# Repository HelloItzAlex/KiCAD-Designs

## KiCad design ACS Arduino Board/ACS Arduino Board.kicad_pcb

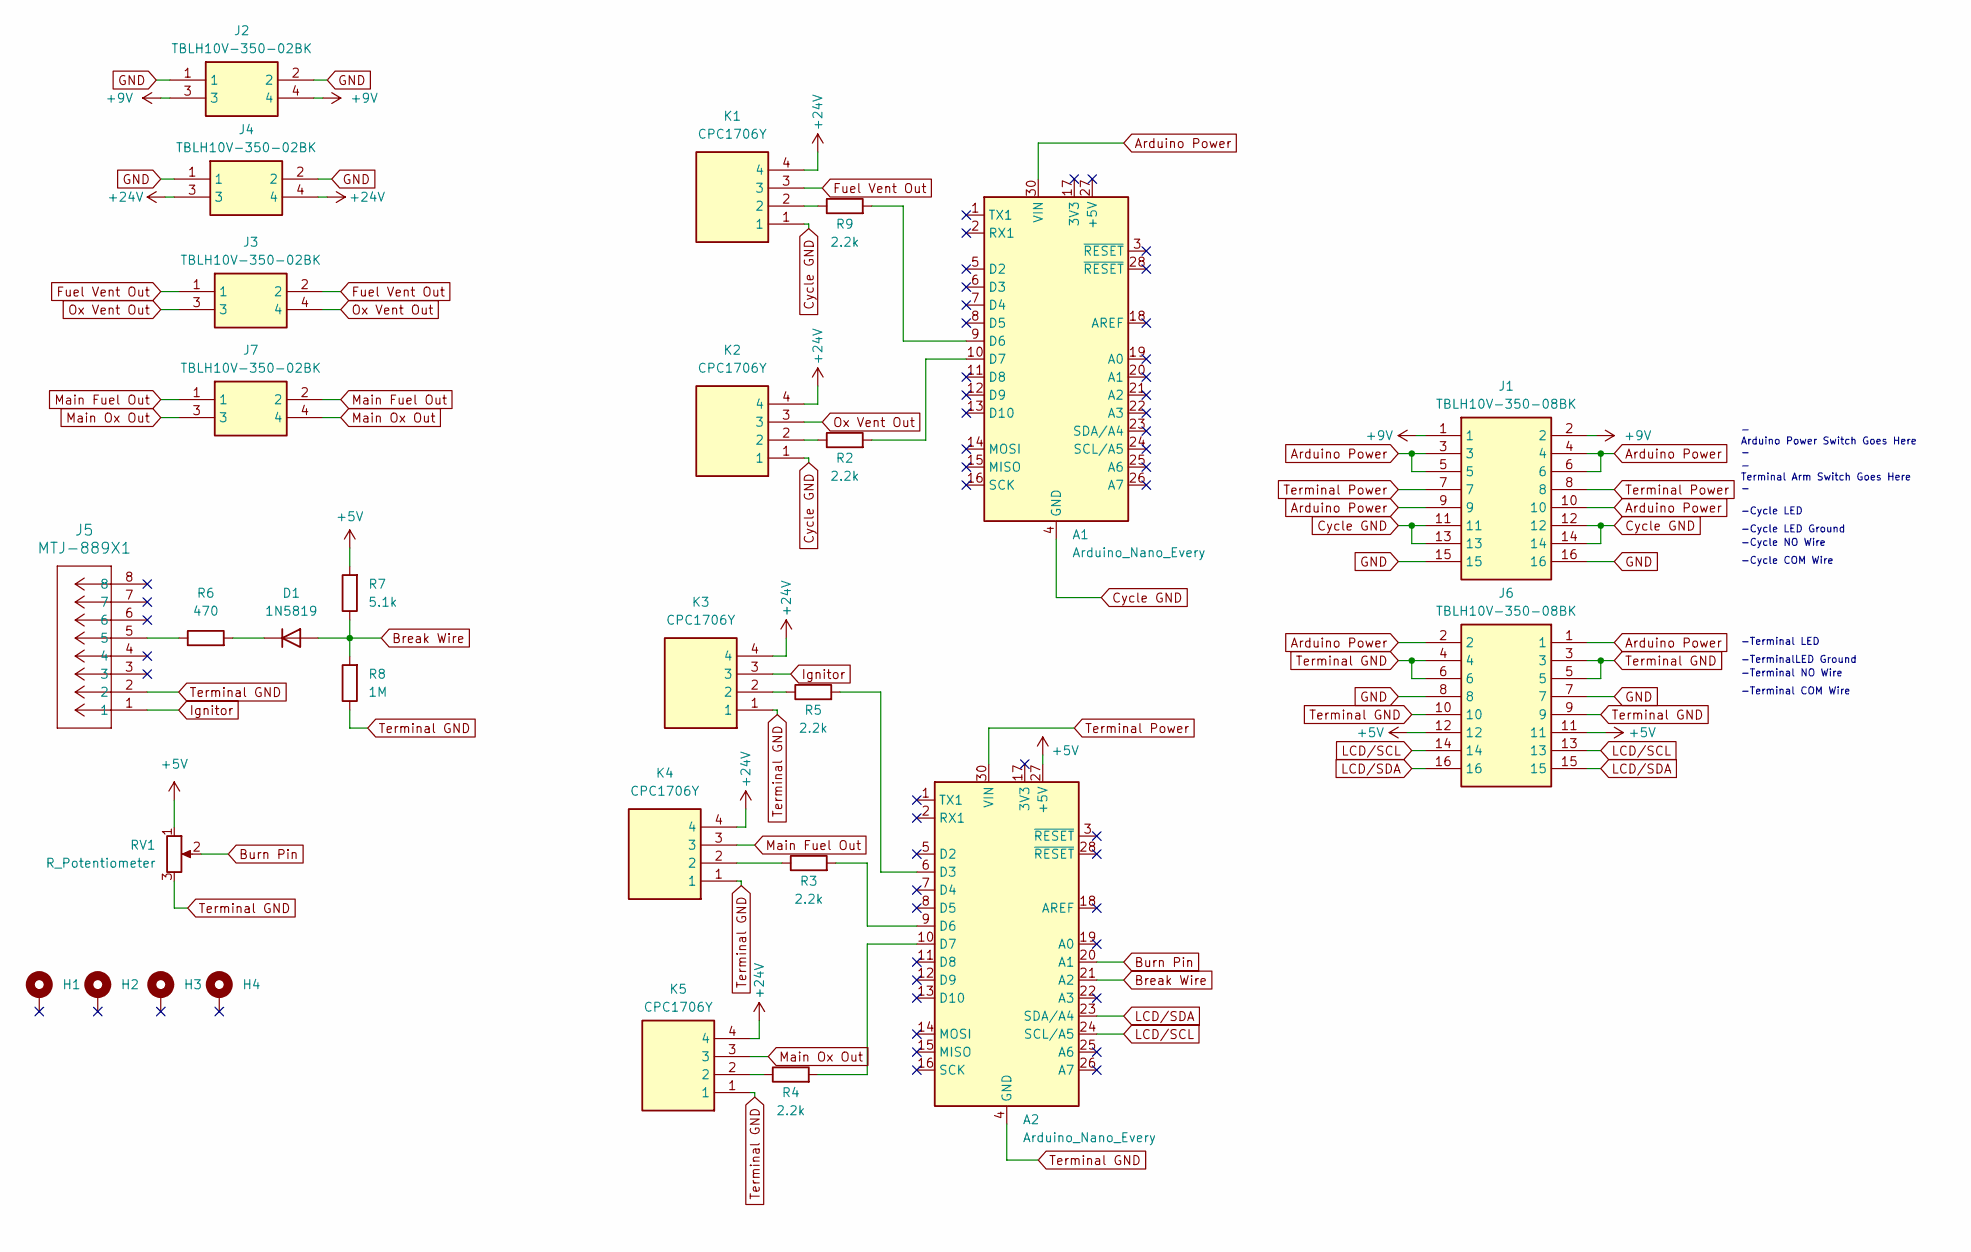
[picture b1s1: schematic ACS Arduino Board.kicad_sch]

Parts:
A1, A2: Arduino_Nano_Every; Arduino_Nano
D1: 1N5819; D_A-405_P7.62mm_Horizontal
H1, H2, H3, H4: MountingHole_Pad; MountingHole_3.2mm_M3_DIN965_Pad_TopBottom
J1, J6: TBLH10V-350-08BK; RHDR16W80P550X350_2X8_2870X850X1420P; Mouser Part Number 490-TBLH10V-350-08BK
J2, J3, J4, J7: TBLH10V-350-02BK; RHDR4W80P550X350_2X2_770X850X1420P; Mouser Part Number 490-TBLH10V-350-02BK
J5: MTJ-889X1; CONN_MTJ-889X1_ADM
K1, K2, K3, K4, K5: CPC1706Y; Mouser Part Number 849-CPC1706Y
R2, R3, R4, R5, R9: 2.2k; R_Axial_DIN0207_L6.3mm_D2.5mm_P7.62mm_Horizontal
R6: 470; R_Axial_DIN0207_L6.3mm_D2.5mm_P7.62mm_Horizontal
R7: 5.1k; R_Axial_DIN0207_L6.3mm_D2.5mm_P7.62mm_Horizontal
R8: 1M; R_Axial_DIN0207_L6.3mm_D2.5mm_P7.62mm_Horizontal
RV1: R_Potentiometer; PinSocket_1x03_P2.54mm_Vertical

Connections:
+5V: A2.27 (+5V), J6.11, J6.12, R7.2, RV1.1
+9V: J1.1, J1.2, J2.3, J2.4
+24V: J4.3, J4.4, K1.4, K2.4, K3.4, K4.4, K5.4
Arduino Power: A1.30 (VIN), J1.3, J1.4, J1.5, J1.6, J1.9, J1.10, J6.1, J6.2
Break Wire: A2.21 (A2), D1.2 (A), R7.1, R8.2
Burn Pin: A2.20 (A1), RV1.2
Cycle GND: A1.4 (GND), A1.29 (GND), J1.11, J1.12, J1.13, J1.14, K1.1, K2.1
Fuel Vent Out: J3.1, J3.2, K1.3
GND: J1.15, J1.16, J2.1, J2.2, J4.1, J4.2, J6.7, J6.8
Ignitor: J5.1, K3.3
LCD/SCL: A2.24 (SCL/A5), J6.13, J6.14
LCD/SDA: A2.23 (SDA/A4), J6.15, J6.16
Main Fuel Out: J7.1, J7.2, K4.3
Main Ox Out: J7.3, J7.4, K5.3
unnamed: A1.9 (D6), R9.2
unnamed: A1.10 (D7), R2.2
unnamed: A2.6 (D3), R5.2
unnamed: A2.9 (D6), R3.2
unnamed: A2.10 (D7), R4.2
unnamed: D1.1 (K), R6.2
unnamed: J5.5, R6.1
unnamed: K1.2, R9.1
unnamed: K2.2, R2.1
unnamed: K3.2, R5.1
unnamed: K4.2, R3.1
unnamed: K5.2, R4.1
Ox Vent Out: J3.3, J3.4, K2.3
Terminal GND: A2.4 (GND), A2.29 (GND), J5.2, J6.3, J6.4, J6.5, J6.6, J6.9, J6.10, K3.1, K4.1, K5.1, R8.1, RV1.3
Terminal Power: A2.30 (VIN), J1.7, J1.8

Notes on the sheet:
-Cycle LED Ground
-Cycle NO Wire
-Cycle LED
- Terminal Arm Switch Goes Here -
-Terminal LED
-TerminalLED Ground
-Terminal COM Wire
- Arduino Power Switch Goes Here -
-Cycle COM Wire
-Terminal NO Wire

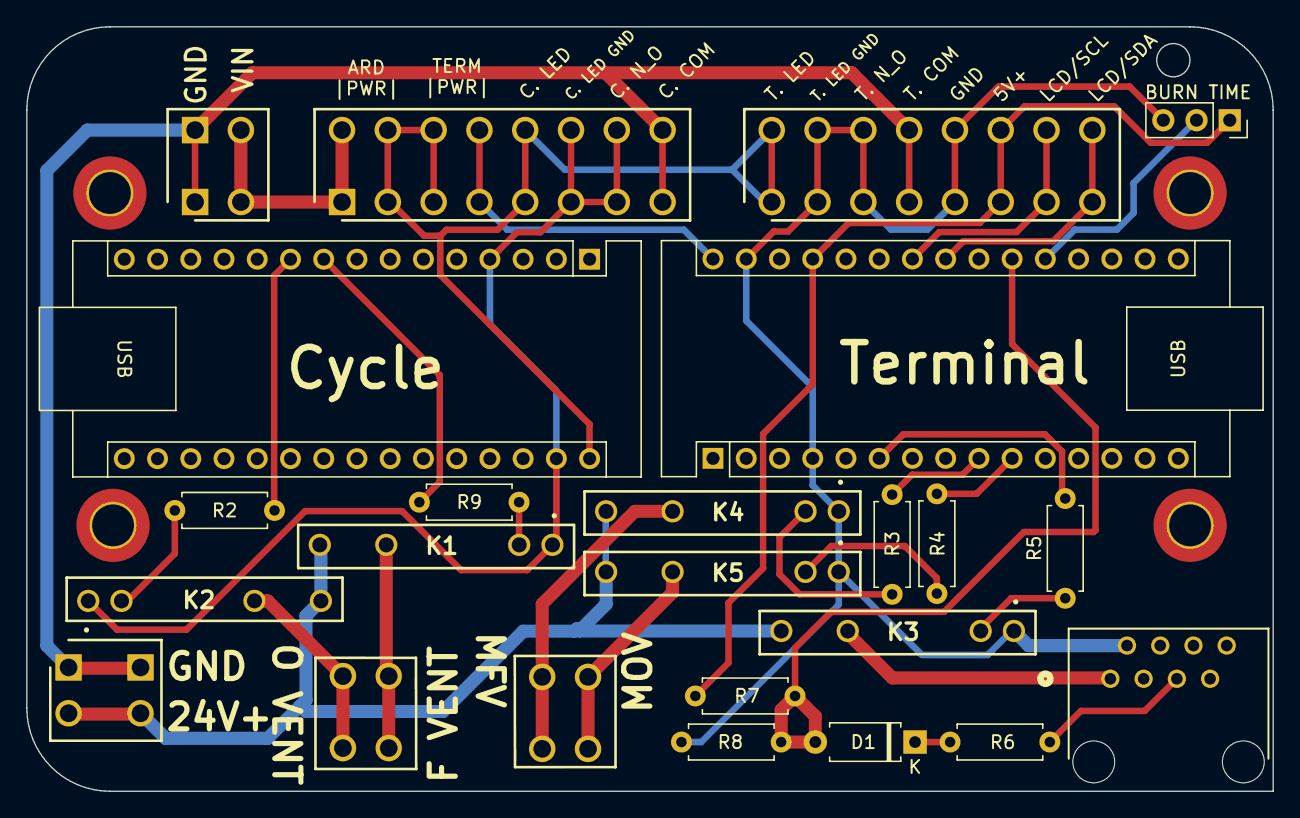
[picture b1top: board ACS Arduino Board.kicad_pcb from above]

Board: 2 copper layers, 95.2 x 58.4 mm, 28 parts (0 on the bottom side), 29 nets.

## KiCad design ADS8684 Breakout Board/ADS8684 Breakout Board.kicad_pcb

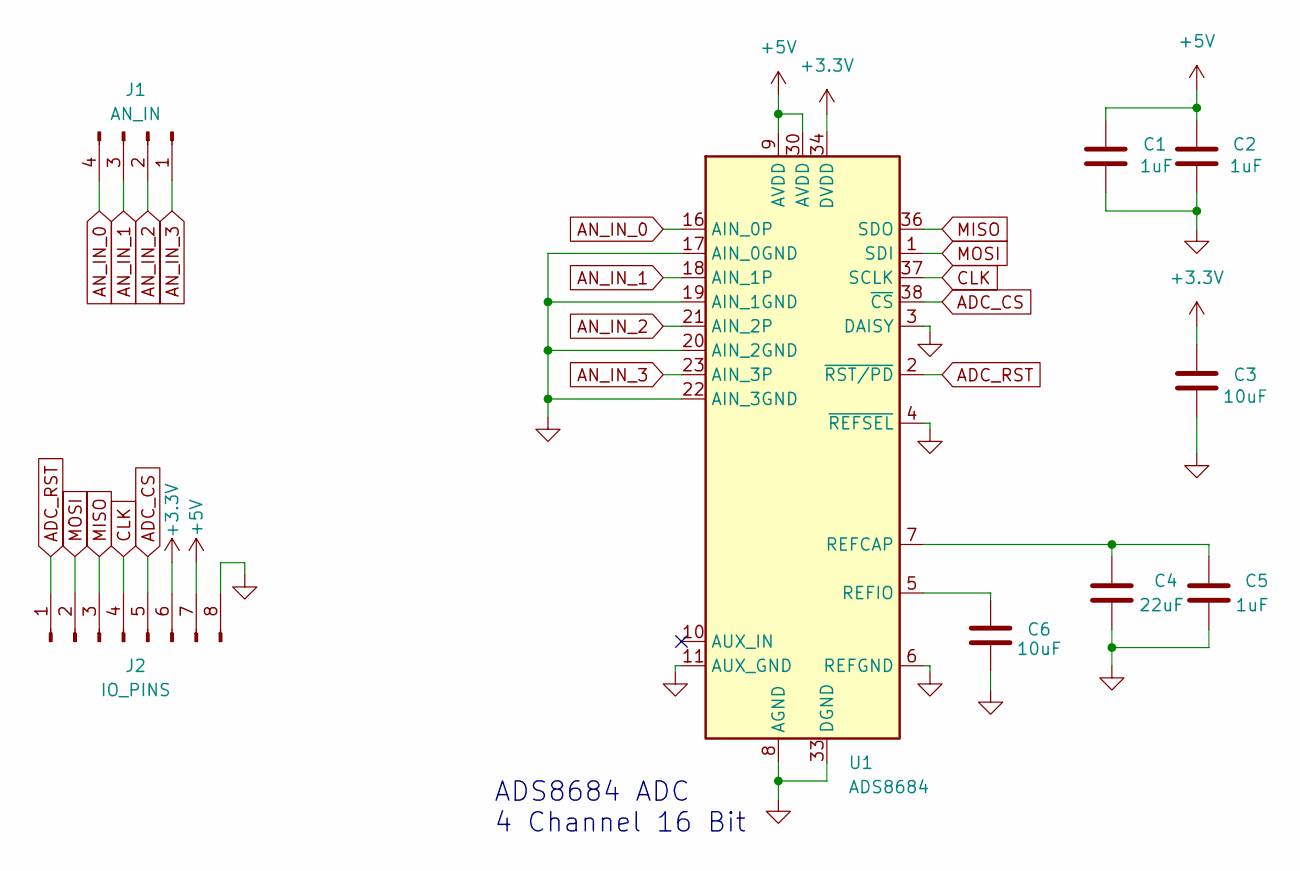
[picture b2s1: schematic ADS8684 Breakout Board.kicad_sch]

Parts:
C1, C2, C5: 1uF; C_0603_1608Metric
C3: 10uF; C_0805_2012Metric
C4: 22uF; C_1210_3225Metric
C6: 10uF; C_0603_1608Metric
J1: AN_IN; PinHeader_1x04_P2.54mm_Vertical
J2: IO_PINS; PinHeader_1x08_P2.54mm_Vertical
U1: ADS8684; TSSOP-38_4.4x9.7mm_P0.5mm

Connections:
+3.3V: C3.2, J2.6, U1.34 (DVDD)
+5V: C1.2, C2.2, J2.7, U1.9 (AVDD), U1.30 (AVDD)
ADC_CS: J2.5, U1.38 (~CS)
ADC_RST: J2.1, U1.2 (~RST/PD)
AN_IN_0: J1.4, U1.16 (AIN_0P)
AN_IN_1: J1.3, U1.18 (AIN_1P)
AN_IN_2: J1.2, U1.21 (AIN_2P)
AN_IN_3: J1.1, U1.23 (AIN_3P)
CLK: J2.4, U1.37 (SCLK)
GND: C1.1, C2.1, C3.1, C4.1, C5.1, C6.2, J2.8, U1.3 (DAISY), U1.4 (~REFSEL), U1.6 (REFGND), U1.8 (AGND), U1.11 (AUX_GND), U1.17 (AIN_0GND), U1.19 (AIN_1GND), U1.20 (AIN_2GND), U1.22 (AIN_3GND), U1.28 (AGND), U1.29 (AGND), U1.31 (AGND), U1.32 (AGND), U1.33 (DGND)
MISO: J2.3, U1.36 (SDO)
MOSI: J2.2, U1.1 (SDI)
unnamed: C4.2, C5.2, U1.7 (REFCAP)
unnamed: C6.1, U1.5 (REFIO)

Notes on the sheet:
ADS8684 ADC 4 Channel 16 Bit

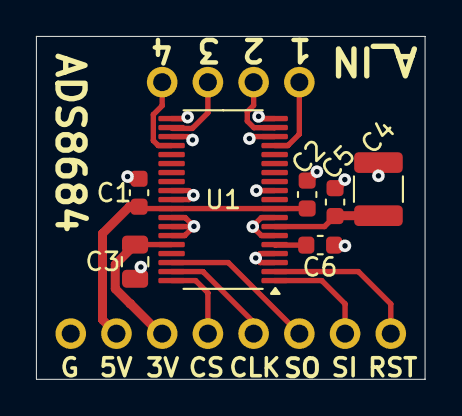
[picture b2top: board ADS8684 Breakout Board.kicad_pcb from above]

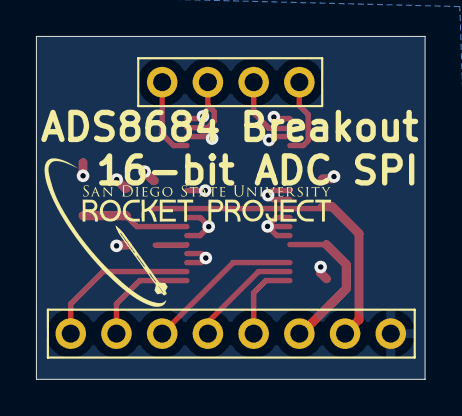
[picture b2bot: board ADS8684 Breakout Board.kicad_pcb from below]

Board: 2 copper layers, 21.6 x 19.1 mm, 9 parts (2 on the bottom side), 14 nets.

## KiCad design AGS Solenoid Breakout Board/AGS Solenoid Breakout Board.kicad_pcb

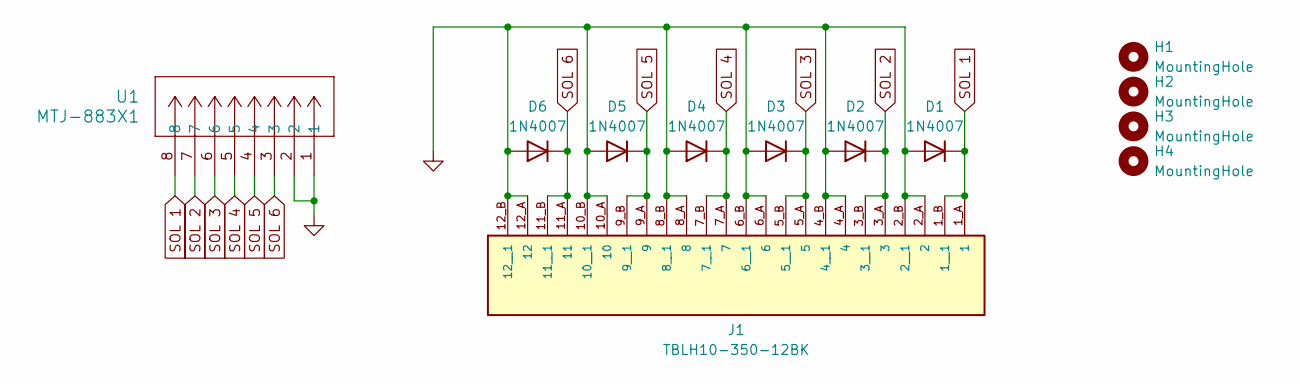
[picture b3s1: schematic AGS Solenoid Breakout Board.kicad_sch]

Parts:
D1, D2, D3, D4, D5, D6: 1N4007; D_DO-41_SOD81_P2.54mm_Vertical_AnodeUp
H1, H2, H3, H4: MountingHole; MountingHole_3.2mm_M3
J1: TBLH10-350-12BK; CUI_TBLH10-350-12BK
U1: MTJ-883X1; CONN_MTJ-883X1_ADM

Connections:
GND: D1.2 (A), D2.2 (A), D3.2 (A), D4.2 (A), D5.2 (A), D6.2 (A), J1.2_A (2), J1.2_B (2__1), J1.4_A (4), J1.4_B (4__1), J1.6_A (6), J1.6_B (6__1), J1.8_A (8), J1.8_B (8__1), J1.10_A (10), J1.10_B (10__1), J1.12_A (12), J1.12_B (12__1), U1.1, U1.2
SOL 1: D1.1 (K), J1.1_A (1), J1.1_B (1__1), U1.8
SOL 2: D2.1 (K), J1.3_A (3), J1.3_B (3__1), U1.7
SOL 3: D3.1 (K), J1.5_A (5), J1.5_B (5__1), U1.6
SOL 4: D4.1 (K), J1.7_A (7), J1.7_B (7__1), U1.5
SOL 5: D5.1 (K), J1.9_A (9), J1.9_B (9__1), U1.4
SOL 6: D6.1 (K), J1.11_A (11), J1.11_B (11__1), U1.3

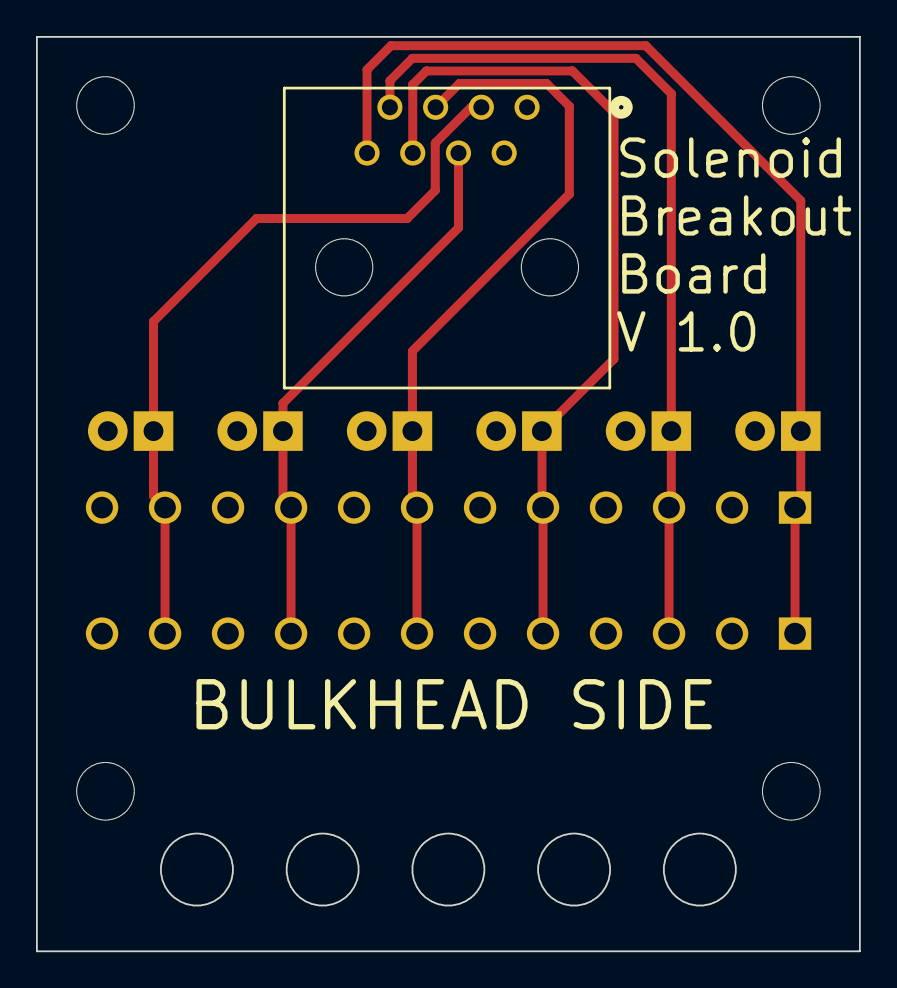
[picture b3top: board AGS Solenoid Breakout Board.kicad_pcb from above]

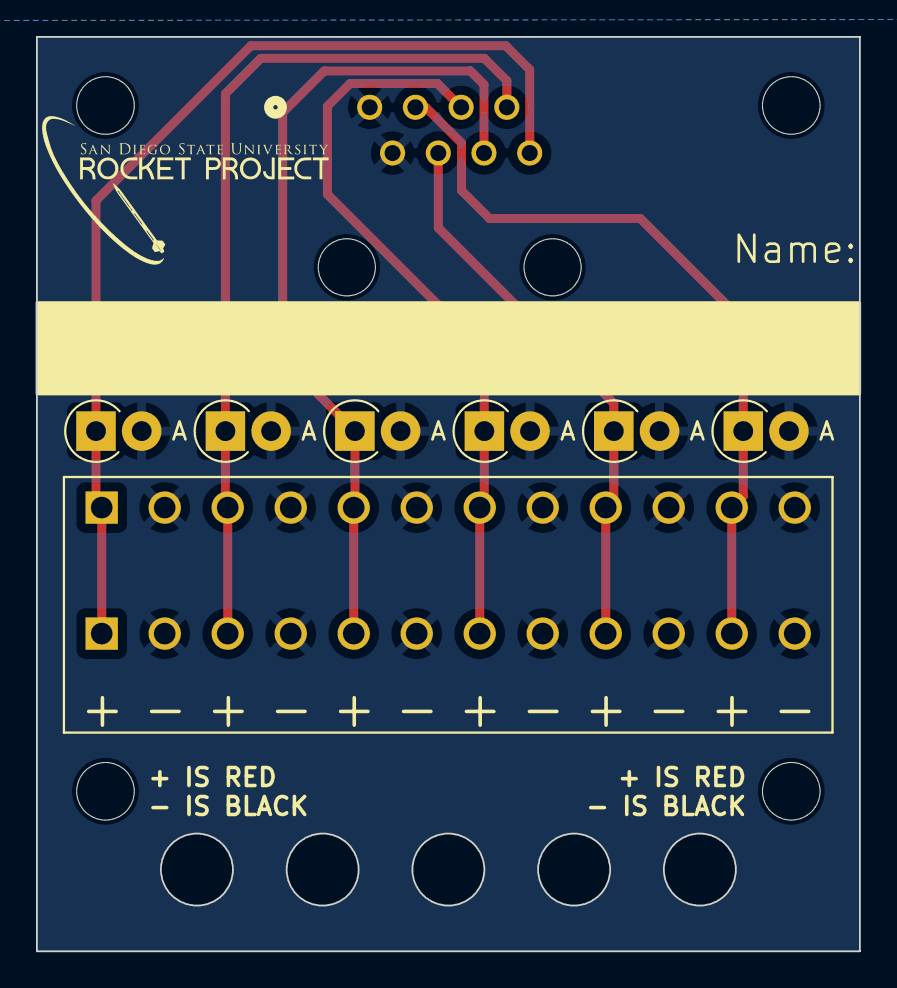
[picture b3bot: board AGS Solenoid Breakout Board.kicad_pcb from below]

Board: 2 copper layers, 45.7 x 50.8 mm, 12 parts (7 on the bottom side), 7 nets.

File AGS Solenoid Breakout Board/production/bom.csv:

Designator,Footprint,Quantity,Value,LCSC Part #
"D1, D2, D3, D4, D5, D6",D_DO-41_SOD81_P2.54mm_Vertical_AnodeUp,6,1N4007,
"H1, H2, H3, H4",MountingHole_3.2mm_M3,4,MountingHole,
J1,CUI_TBLH10-350-12BK,1,TBLH10-350-12BK,
U1,CONN_MTJ-883X1_ADM,1,MTJ-883X1,

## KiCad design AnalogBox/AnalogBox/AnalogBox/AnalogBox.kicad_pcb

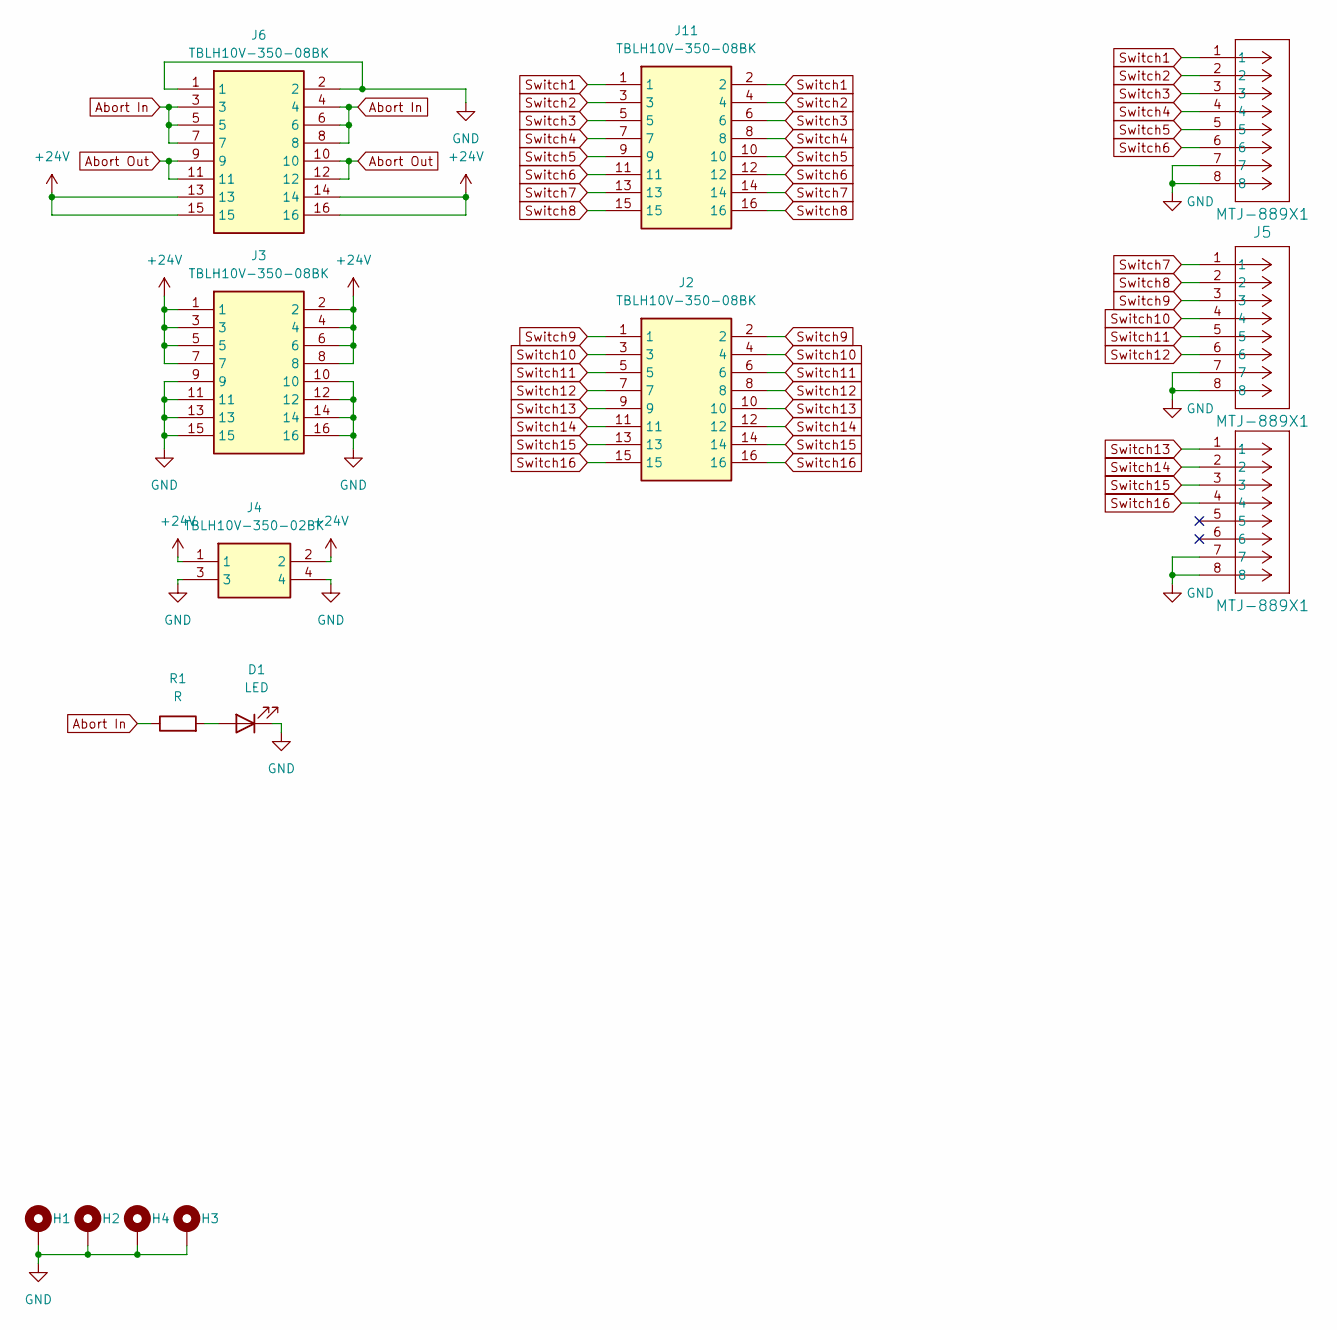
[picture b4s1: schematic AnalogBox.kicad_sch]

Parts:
D1: LED; LED_D3.0mm
H1, H2, H3, H4: MountingHole_Pad; MountingHole_3.2mm_M3_Pad_TopBottom
J1, J5, J8: MTJ-889X1; CONN_MTJ-889X1_ADM
J2, J3, J6, J11: TBLH10V-350-08BK; RHDR16W80P550X350_2X8_2870X850X1420P; Mouser Part Number 490-TBLH10V-350-08BK
J4: TBLH10V-350-02BK; RHDR4W80P550X350_2X2_770X850X1420P; Mouser Part Number 490-TBLH10V-350-02BK
R1: R; R_Axial_DIN0207_L6.3mm_D2.5mm_P7.62mm_Horizontal

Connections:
+24V: J3.1, J3.2, J3.3, J3.4, J3.5, J3.6, J3.7, J3.8, J4.1, J4.2, J6.13, J6.14, J6.15, J6.16
Abort In: J6.3, J6.4, J6.5, J6.6, J6.7, J6.8, R1.1
Abort Out: J6.9, J6.10, J6.11, J6.12
GND: D1.1 (K), H1.1, H2.1, H3.1, H4.1, J1.7, J1.8, J3.9, J3.10, J3.11, J3.12, J3.13, J3.14, J3.15, J3.16, J4.3, J4.4, J5.7, J5.8, J6.1, J6.2, J8.7, J8.8
unnamed: D1.2 (A), R1.2
Switch1: J5.1, J11.1, J11.2
Switch2: J5.2, J11.3, J11.4
Switch3: J5.3, J11.5, J11.6
Switch4: J5.4, J11.7, J11.8
Switch5: J5.5, J11.9, J11.10
Switch6: J5.6, J11.11, J11.12
Switch7: J1.1, J11.13, J11.14
Switch8: J1.2, J11.15, J11.16
Switch9: J1.3, J2.1, J2.2
Switch10: J1.4, J2.3, J2.4
Switch11: J1.5, J2.5, J2.6
Switch12: J1.6, J2.7, J2.8
Switch13: J2.9, J2.10, J8.1
Switch14: J2.11, J2.12, J8.2
Switch15: J2.13, J2.14, J8.3
Switch16: J2.15, J2.16, J8.4

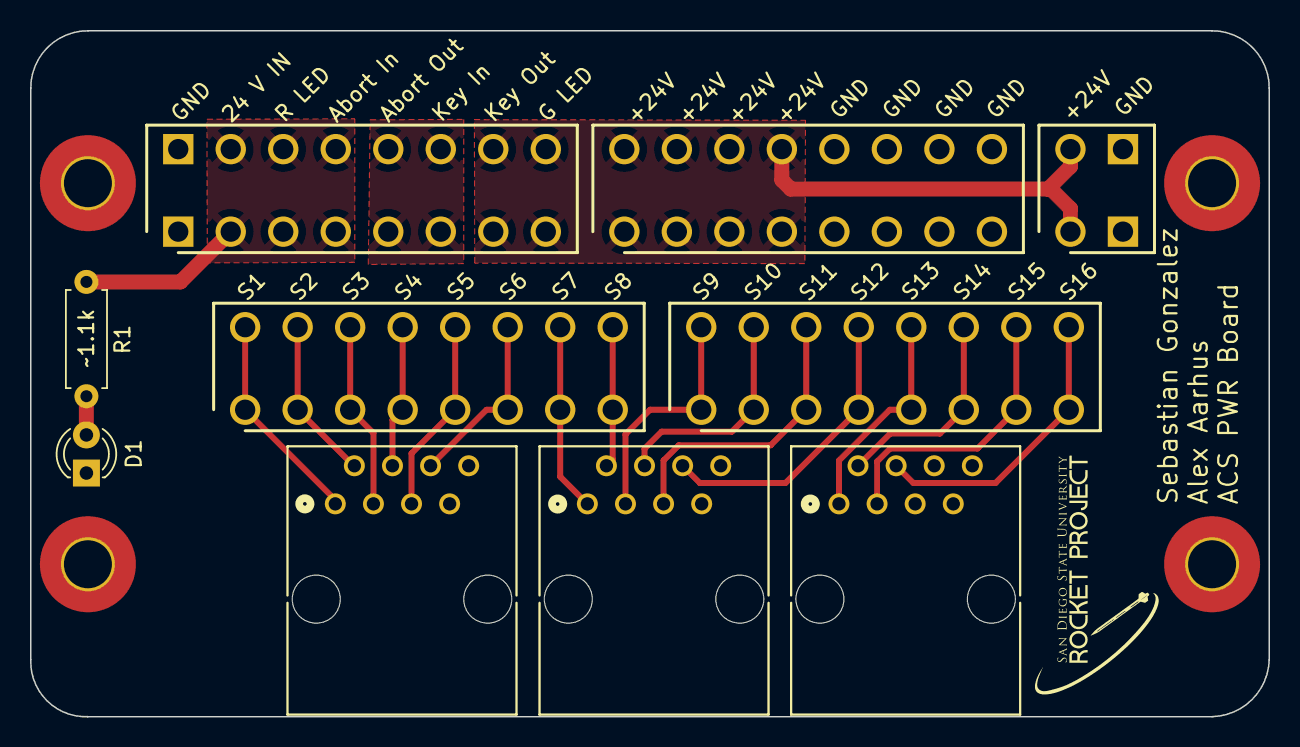
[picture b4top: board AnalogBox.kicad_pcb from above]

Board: 2 copper layers, 82.6 x 45.7 mm, 14 parts (0 on the bottom side), 21 nets.

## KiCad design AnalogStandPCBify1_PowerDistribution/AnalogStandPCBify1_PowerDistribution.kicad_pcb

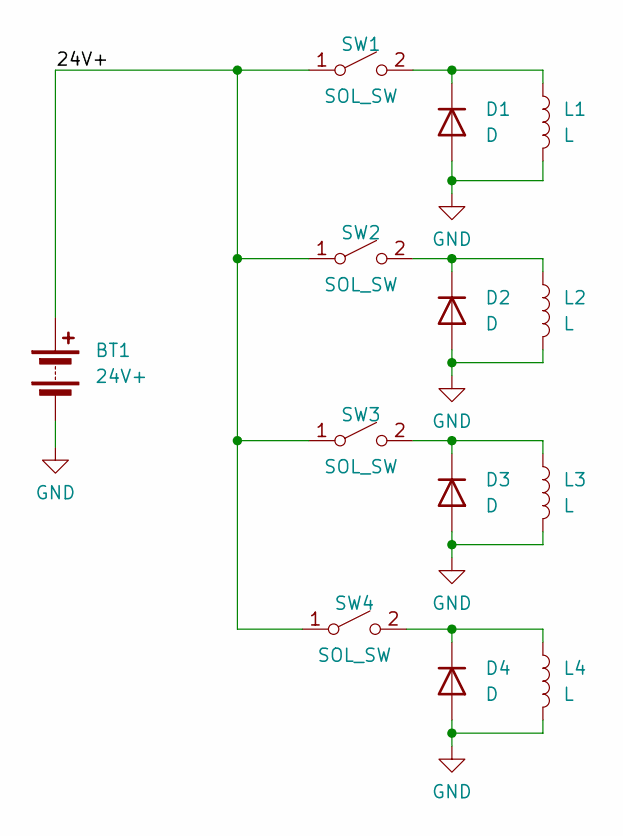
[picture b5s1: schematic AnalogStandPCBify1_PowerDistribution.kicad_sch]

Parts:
BT1: 24V+; SolderWire-1.5sqmm_1x02_P7.8mm_D1.7mm_OD3.9mm_Relief
D1, D2, D3, D4: D; D_A-405_P7.62mm_Horizontal
L1, L2, L3, L4: L; SolderWire-1sqmm_1x02_P5.4mm_D1.4mm_OD2.7mm_Relief
SW1, SW2, SW3, SW4: SOL_SW; SolderWire-1.5sqmm_1x02_P7.8mm_D1.7mm_OD3.9mm_Relief

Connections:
/24V+: BT1.1 (+), SW1.1 (A), SW2.1 (A), SW3.1 (A), SW4.1 (A)
GND: BT1.2 (-), D1.2 (A), D2.2 (A), D3.2 (A), D4.2 (A), L1.2, L2.2, L3.2, L4.2
unnamed: D1.1 (K), L1.1, SW1.2 (B)
unnamed: D2.1 (K), L2.1, SW2.2 (B)
unnamed: D3.1 (K), L3.1, SW3.2 (B)
unnamed: D4.1 (K), L4.1, SW4.2 (B)

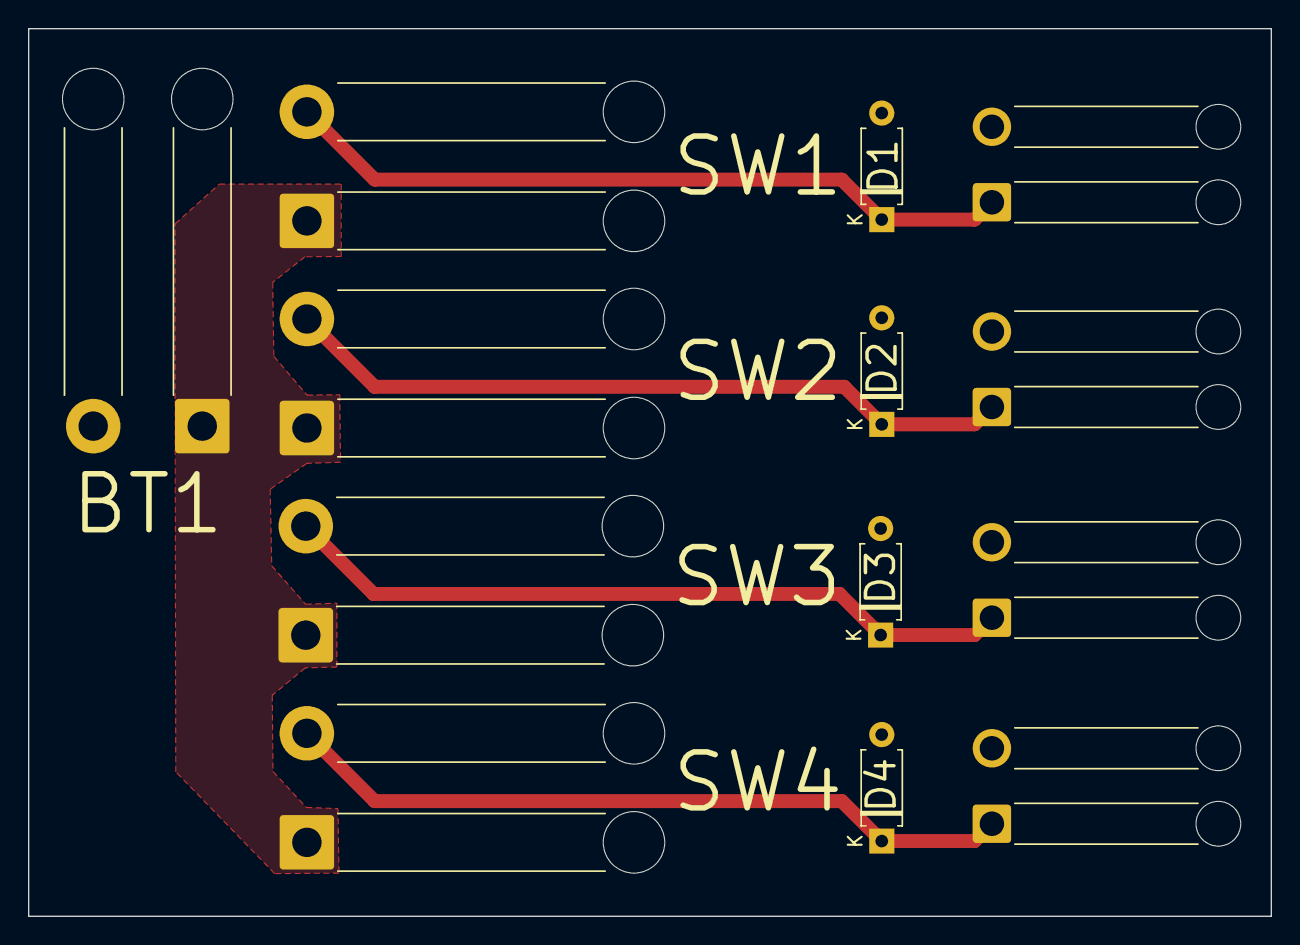
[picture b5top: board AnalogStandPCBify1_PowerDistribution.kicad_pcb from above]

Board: 2 copper layers, 88.9 x 63.5 mm, 13 parts (0 on the bottom side), 6 nets.

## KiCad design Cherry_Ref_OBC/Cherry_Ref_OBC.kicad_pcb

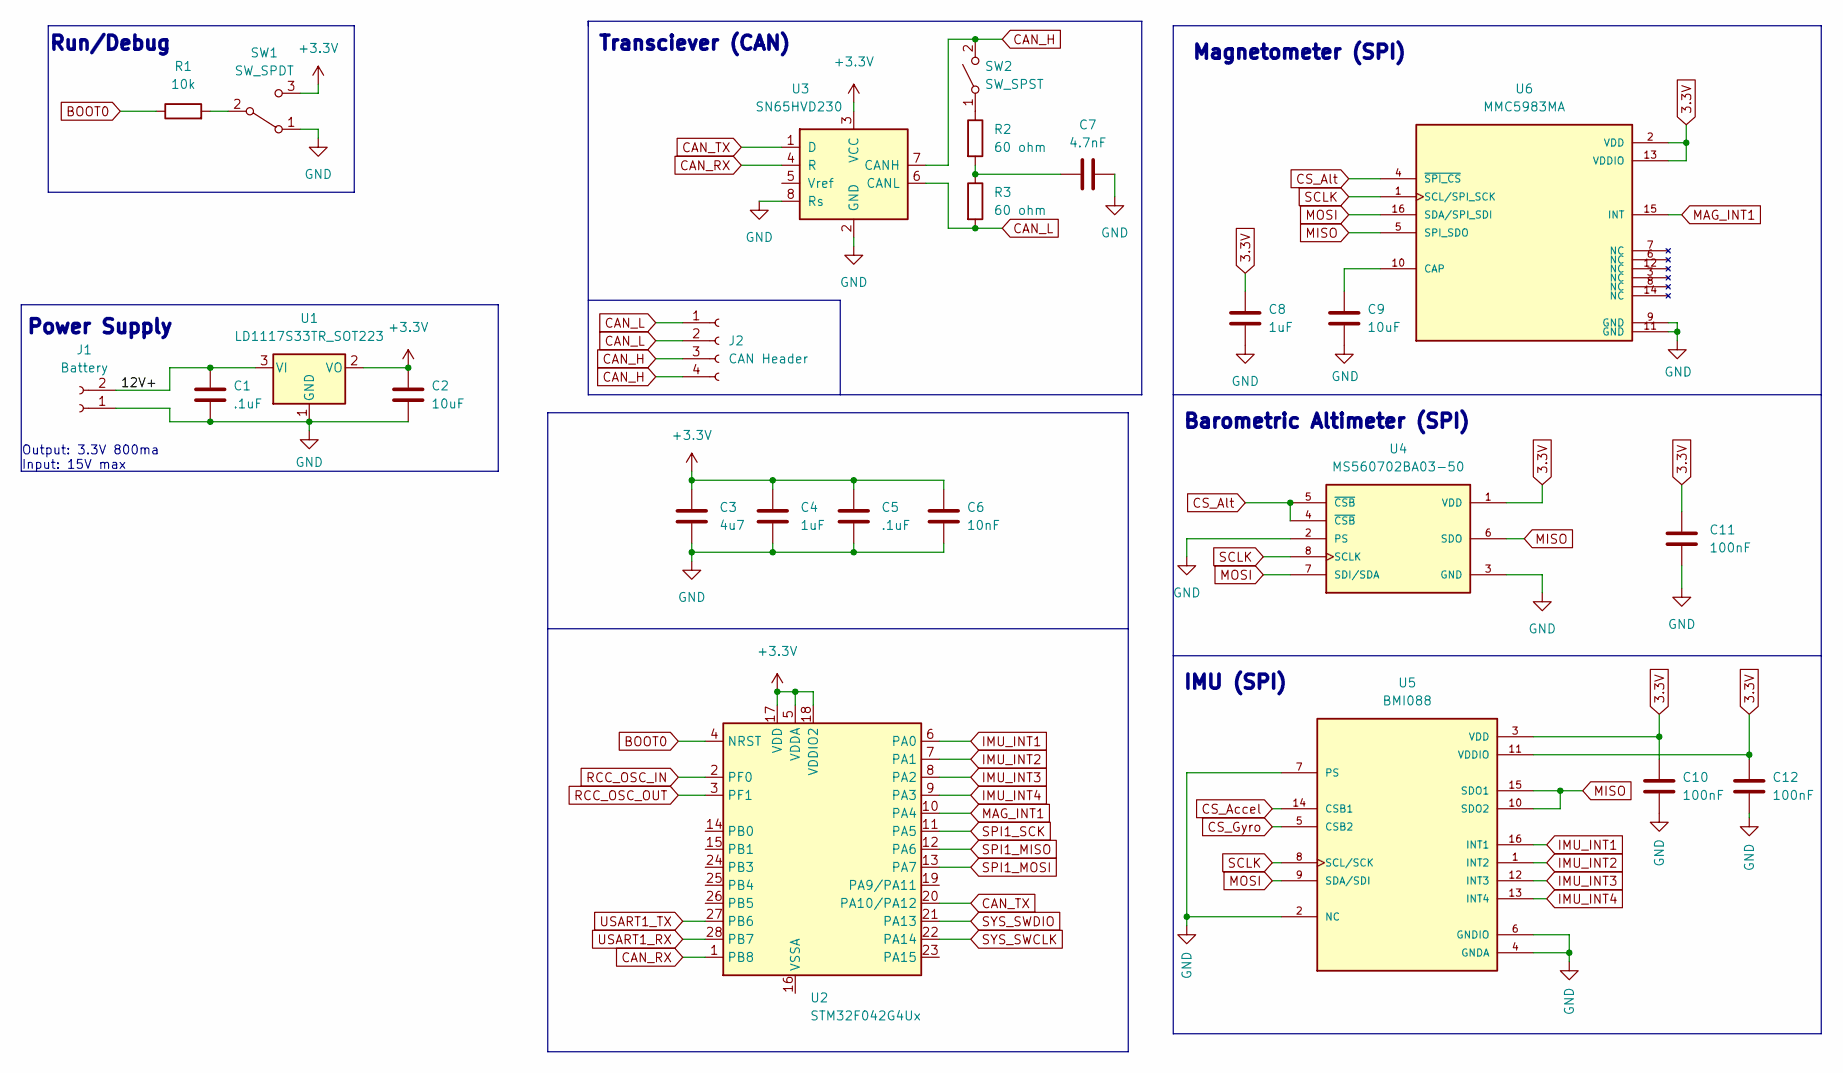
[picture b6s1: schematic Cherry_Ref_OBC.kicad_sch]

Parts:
C1, C5: .1uF; C_0402_1005Metric
C2: 10uF; C_0603_1608Metric
C3: 4u7; C_0402_1005Metric
C4, C8: 1uF; C_0402_1005Metric
C6: 10nF; C_0402_1005Metric
C7: 4.7nF; C_0402_1005Metric
C9: 10uF; C_0402_1005Metric
C10, C11, C12: 100nF; C_0402_1005Metric
J1: Battery; PinHeader_1x02_P1.00mm_Vertical
J2: CAN Header; PinHeader_1x04_P1.00mm_Vertical
R1: 10k; R_0402_1005Metric
R2, R3: 60 ohm; R_0805_2012Metric
SW1: SW_SPDT; SolderJumper-3_P1.3mm_Open_RoundedPad1.0x1.5mm_NumberLabels
SW2: SW_SPST; SolderJumper-2_P1.3mm_Open_RoundedPad1.0x1.5mm
U1: LD1117S33TR_SOT223; SOT-223-3_TabPin2
U2: STM32F042G4Ux; QFN-28_4x4mm_P0.5mm
U3: SN65HVD230; SOIC-8_3.9x4.9mm_P1.27mm
U4: MS560702BA03-50; SON125P300X500X100-8N
U5: BMI088; PQFN50P450X300X100-16N
U6: MMC5983MA; PQFN50P300X300X100-16N; PARTREV A

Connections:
3.3V: C8.1, C10.1, C11.1, C12.1, U4.1 (VDD), U5.3 (VDD), U5.11 (VDDIO), U6.2 (VDD), U6.13 (VDDIO)
+3.3V: C2.1, C3.1, C4.1, C5.1, C6.1, SW1.3 (C), U1.2 (VO), U2.5 (VDDA), U2.17 (VDD), U2.18 (VDDIO2), U3.3 (VCC)
/12V+: C1.1, J1.2, U1.3 (VI)
BOOT0: R1.1, U2.4 (NRST)
CAN_H: J2.3, J2.4, SW2.2 (B), U3.7 (CANH)
CAN_L: J2.1, J2.2, R3.2, U3.6 (CANL)
CAN_RX: U2.1 (PB8), U3.4 (R)
CAN_TX: U2.20 (PA10/PA12), U3.1 (D)
CS_Accel: U5.14 (CSB1)
CS_Alt: U4.4 (~CSB), U4.5 (~CSB), U6.4 (~SPI_CS)
CS_Gyro: U5.5 (CSB2)
GND: C1.2, C2.2, C3.2, C4.2, C5.2, C6.2, C7.2, C8.2, C9.2, C10.2, C11.2, C12.2, J1.1, SW1.1 (A), U1.1 (GND), U3.2 (GND), U3.8 (Rs), U4.2 (PS), U4.3 (GND), U5.2 (NC), U5.4 (GNDA), U5.6 (GNDIO), U5.7 (PS), U6.9 (GND), U6.11 (GND)
IMU_INT1: U2.6 (PA0), U5.16 (INT1)
IMU_INT2: U2.7 (PA1), U5.1 (INT2)
IMU_INT3: U2.8 (PA2), U5.12 (INT3)
IMU_INT4: U2.9 (PA3), U5.13 (INT4)
MAG_INT1: U2.10 (PA4), U6.15 (INT)
MISO: U4.6 (SDO), U5.10 (SDO2), U5.15 (SDO1), U6.5 (SPI_SDO)
MOSI: U4.7 (SDI/SDA), U5.9 (SDA/SDI), U6.16 (SDA/SPI_SDI)
unnamed: C7.1, R2.2, R3.1
unnamed: C9.1, U6.10 (CAP)
unnamed: R1.2, SW1.2 (B)
unnamed: R2.1, SW2.1 (A)
RCC_OSC_IN: U2.2 (PF0)
RCC_OSC_OUT: U2.3 (PF1)
SCLK: U4.8 (SCLK), U5.8 (SCL/SCK), U6.1 (SCL/SPI_SCK)
SPI1_MISO: U2.12 (PA6)
SPI1_MOSI: U2.13 (PA7)
SPI1_SCK: U2.11 (PA5)
SYS_SWCLK: U2.22 (PA14)
SYS_SWDIO: U2.21 (PA13)
USART1_RX: U2.28 (PB7)
USART1_TX: U2.27 (PB6)

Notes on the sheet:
Output: 3.3V 800ma Input: 15V max
Magnetometer (SPI)
Run/Debug
Power Supply
Transciever (CAN)
Barometric Altimeter (SPI)
IMU (SPI)

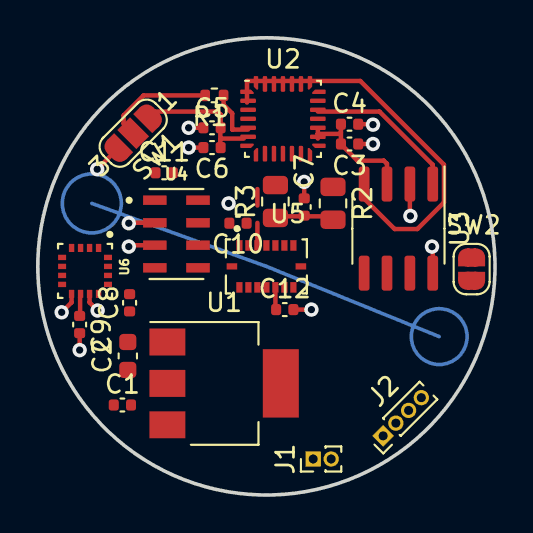
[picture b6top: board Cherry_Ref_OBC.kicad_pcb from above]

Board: 2 copper layers, 25.4 x 25.4 mm, 25 parts (0 on the bottom side), 22 nets.
